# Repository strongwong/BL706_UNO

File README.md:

# BL706_UNO
The hardware design of BL706 UNO is based on BL706 module; it has been verified to function properly.

# Showcase

## 3D view

## BL706 UNO picture

## Test

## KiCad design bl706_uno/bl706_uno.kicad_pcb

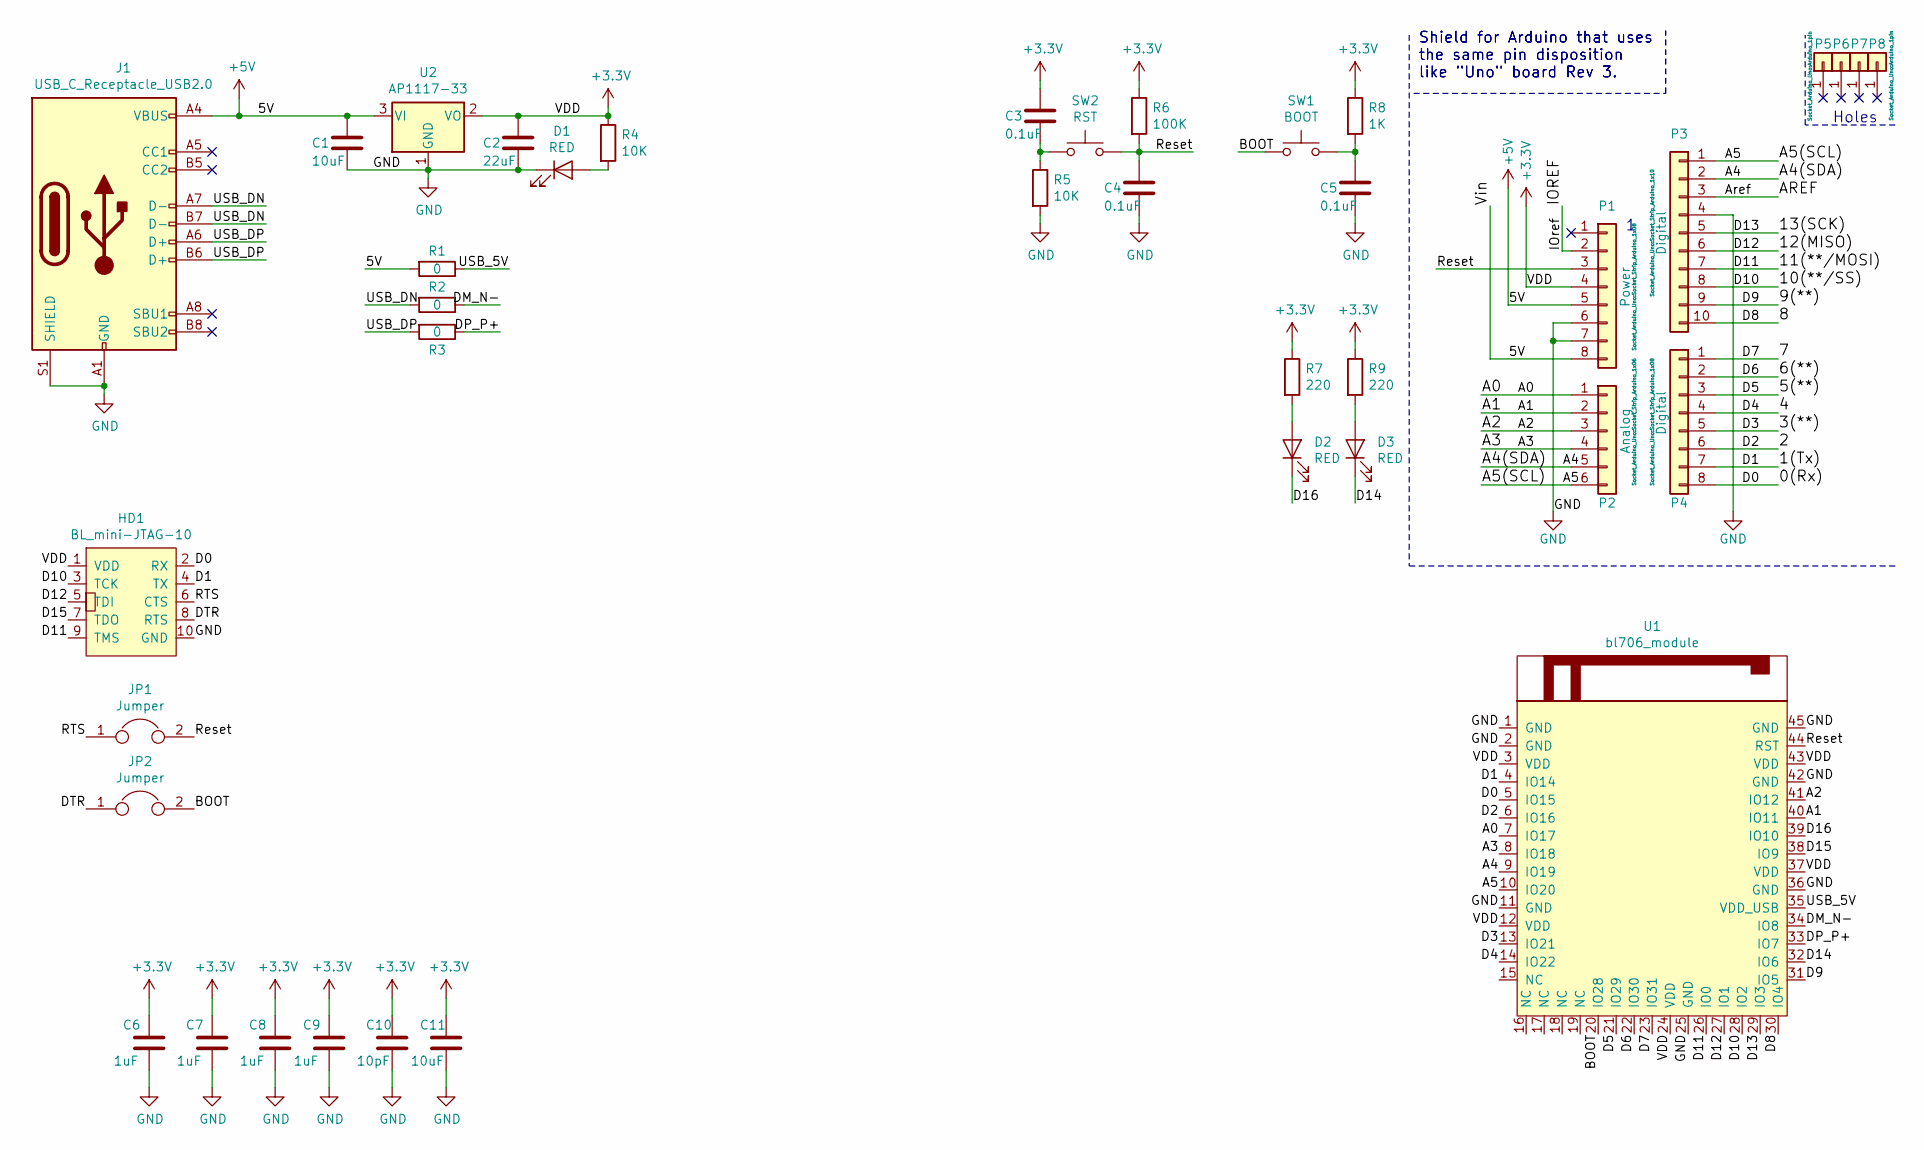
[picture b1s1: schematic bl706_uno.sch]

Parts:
C1, C11: 10uF; C_0603_1608Metric
C2: 22uF; C_0603_1608Metric
C3, C4, C5: 0.1uF; C_0603_1608Metric
C6, C7, C8, C9: 1uF; C_0603_1608Metric
C10: 10pF; C_0603_1608Metric
D1, D2, D3: RED; D_0603_1608Metric
HD1: BL_mini-JTAG-10; PinHeader_2x05_P1.27mm_Vertical
J1: USB_C_Receptacle_USB2.0; USB_C_Receptacle_Palconn_UTC16-G
JP1, JP2: Jumper; PinHeader_1x02_P2.54mm_Vertical
P1: Power; Socket_Strip_Arduino_1x08
P2: Analog; Socket_Strip_Arduino_1x06
P3: Digital; Socket_Strip_Arduino_1x10
P4: Digital; Socket_Strip_Arduino_1x08
P5, P6, P7, P8: CONN_01X01; Arduino_1pin
R1, R2, R3: 0; R_0603_1608Metric
R4, R5: 10K; R_0603_1608Metric
R6: 100K; R_0603_1608Metric
R7, R9: 220; R_0603_1608Metric
R8: 1K; R_0603_1608Metric
SW1: BOOT; SW_Push_1P1T_NO_Vertical_Wuerth_434133025816
SW2: RST; SW_Push_1P1T_NO_Vertical_Wuerth_434133025816
U1: bl706_module; bl70x_module
U2: AP1117-33; SOT-223-3_TabPin2

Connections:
+3V3: C2.1, C3.1, C6.1, C7.1, C8.1, C9.1, C10.1, C11.1, HD1.1 (VDD), P1.4, R4.1, R6.1, R7.1, R8.1, R9.1, U1.3 (VDD), U1.12 (VDD), U1.24 (VDD), U1.37 (VDD), U1.43 (VDD), U2.2 (VO)
+5V: C1.1, J1.A4 (VBUS), J1.A9 (VBUS), J1.B4 (VBUS), J1.B9 (VBUS), P1.5, P1.8, R1.2, U2.3 (VI); also elsewhere on the board
/0(Rx): HD1.2 (RX), P4.8, U1.5 (IO15)
/1(Tx): HD1.4 (TX), P4.7, U1.4 (IO14)
/2: P4.6, U1.6 (IO16)
/3(**): P4.5, U1.13 (IO21)
/4: P4.4, U1.14 (IO22)
/5(**): P4.3, U1.21 (IO29)
/6(**): P4.2, U1.22 (IO30)
/7: P4.1, U1.23 (IO31)
/8: P3.10, U1.30 (IO4)
/9(**): P3.9, U1.31 (IO5)
/10(**/SS): HD1.3 (TCK), P3.8, U1.28 (IO2)
/11(**/MOSI): HD1.9 (TMS), P3.7, U1.26 (IO0)
/12(MISO): HD1.5 (TDI), P3.6, U1.27 (IO1)
/13(SCK): P3.5, U1.29 (IO3)
/A0: P2.1, U1.7 (IO17)
/A1: P2.2, U1.40 (IO11)
/A2: P2.3, U1.41 (IO12)
/A3: P2.4, U1.8 (IO18)
/A4: P2.5, P3.2, U1.9 (IO19)
/A5: P2.6, P3.1, U1.10 (IO20)
/AREF: P3.3
/BOOT: JP2.2, SW1.1, U1.20 (IO28); also elsewhere on the board
/D14: D3.1 (K), U1.32 (IO6)
/D15: HD1.7 (TDO), U1.38 (IO9)
/D16: D2.1 (K), U1.39 (IO10)
/DM_N-: R2.1, U1.34 (IO8)
/DP_P+: R3.1, U1.33 (IO7)
/DTR: HD1.8 (RTS), JP2.1
/IOREF: P1.2
/RTS: HD1.6 (CTS), JP1.1
/Reset: C4.1, JP1.2, P1.3, R6.2, SW2.2, U1.44 (RST); also elsewhere on the board
/USB_5V: R1.1, U1.35 (VDD_USB)
/USB_DN: J1.A7 (D-), J1.B7 (D-), R2.2; also elsewhere on the board
/USB_DP: J1.A6 (D+), J1.B6 (D+), R3.2; also elsewhere on the board
GND: C1.2, C2.2, C4.2, C5.2, C6.2, C7.2, C8.2, C9.2, C10.2, C11.2, D1.1 (K), HD1.10 (GND), J1.A1 (GND), J1.A12 (GND), J1.B1 (GND), J1.B12 (GND), J1.S1 (SHIELD), P1.6, P1.7, P3.4, R5.2, U1.1 (GND), U1.2 (GND), U1.11 (GND), U1.25 (GND), U1.36 (GND), U1.42 (GND), U1.45 (GND), U2.1 (GND); also elsewhere on the board
unnamed 37: C3.2, R5.1, SW2.1; also elsewhere on the board
unnamed 38: C5.1, R8.2, SW1.2; also elsewhere on the board
unnamed: D1.2 (A), R4.2
unnamed: D2.2 (A), R7.2
unnamed: D3.2 (A), R9.2

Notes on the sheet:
Shield for Arduino that uses the same pin disposition like "Uno" board Rev 3.
Holes

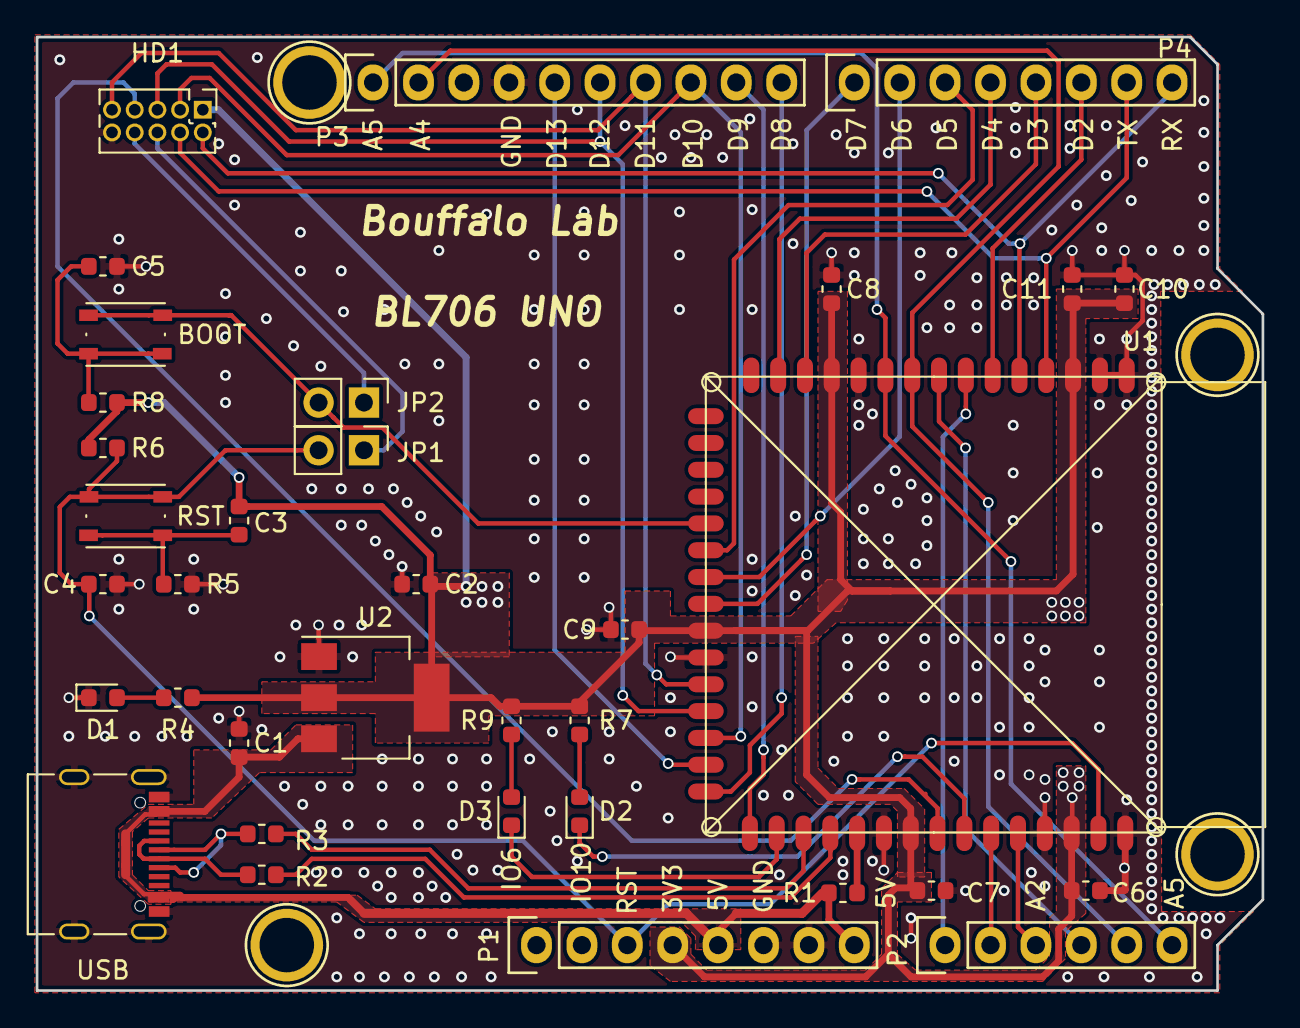
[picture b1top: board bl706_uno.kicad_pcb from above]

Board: 2 copper layers, 68.6 x 53.3 mm, 39 parts (0 on the bottom side), 40 nets.

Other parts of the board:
BOOT: BOOT; SW_Push_1P1T_NO_Vertical_Wuerth_434133025816
RST: RST; SW_Push_1P1T_NO_Vertical_Wuerth_434133025816
USB: USB_C_Receptacle_USB2.0; USB_C_Receptacle_Palconn_UTC16-G

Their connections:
+5V: USB.A4, USB.A9, USB.B4, USB.B9; also elsewhere on the board
/BOOT: BOOT.1; also elsewhere on the board
/Reset: RST.2; also elsewhere on the board
/USB_DN: USB.A7, USB.B7; also elsewhere on the board
/USB_DP: USB.A6, USB.B6; also elsewhere on the board
GND: USB.A1, USB.A12, USB.B1, USB.B12, USB.S1; also elsewhere on the board
unnamed 37: RST.1; also elsewhere on the board
unnamed 38: BOOT.2; also elsewhere on the board

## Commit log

2021-08-07 add bl706 uno pcb design base on bl706 module
2021-08-08 add bl706 module Schematic symbol and PCB footprint librarie
2021-08-14 update bl706_uno project and add pdf
2021-08-14 add img and update readme
2021-08-14 update bl706 module size,more accurate now
